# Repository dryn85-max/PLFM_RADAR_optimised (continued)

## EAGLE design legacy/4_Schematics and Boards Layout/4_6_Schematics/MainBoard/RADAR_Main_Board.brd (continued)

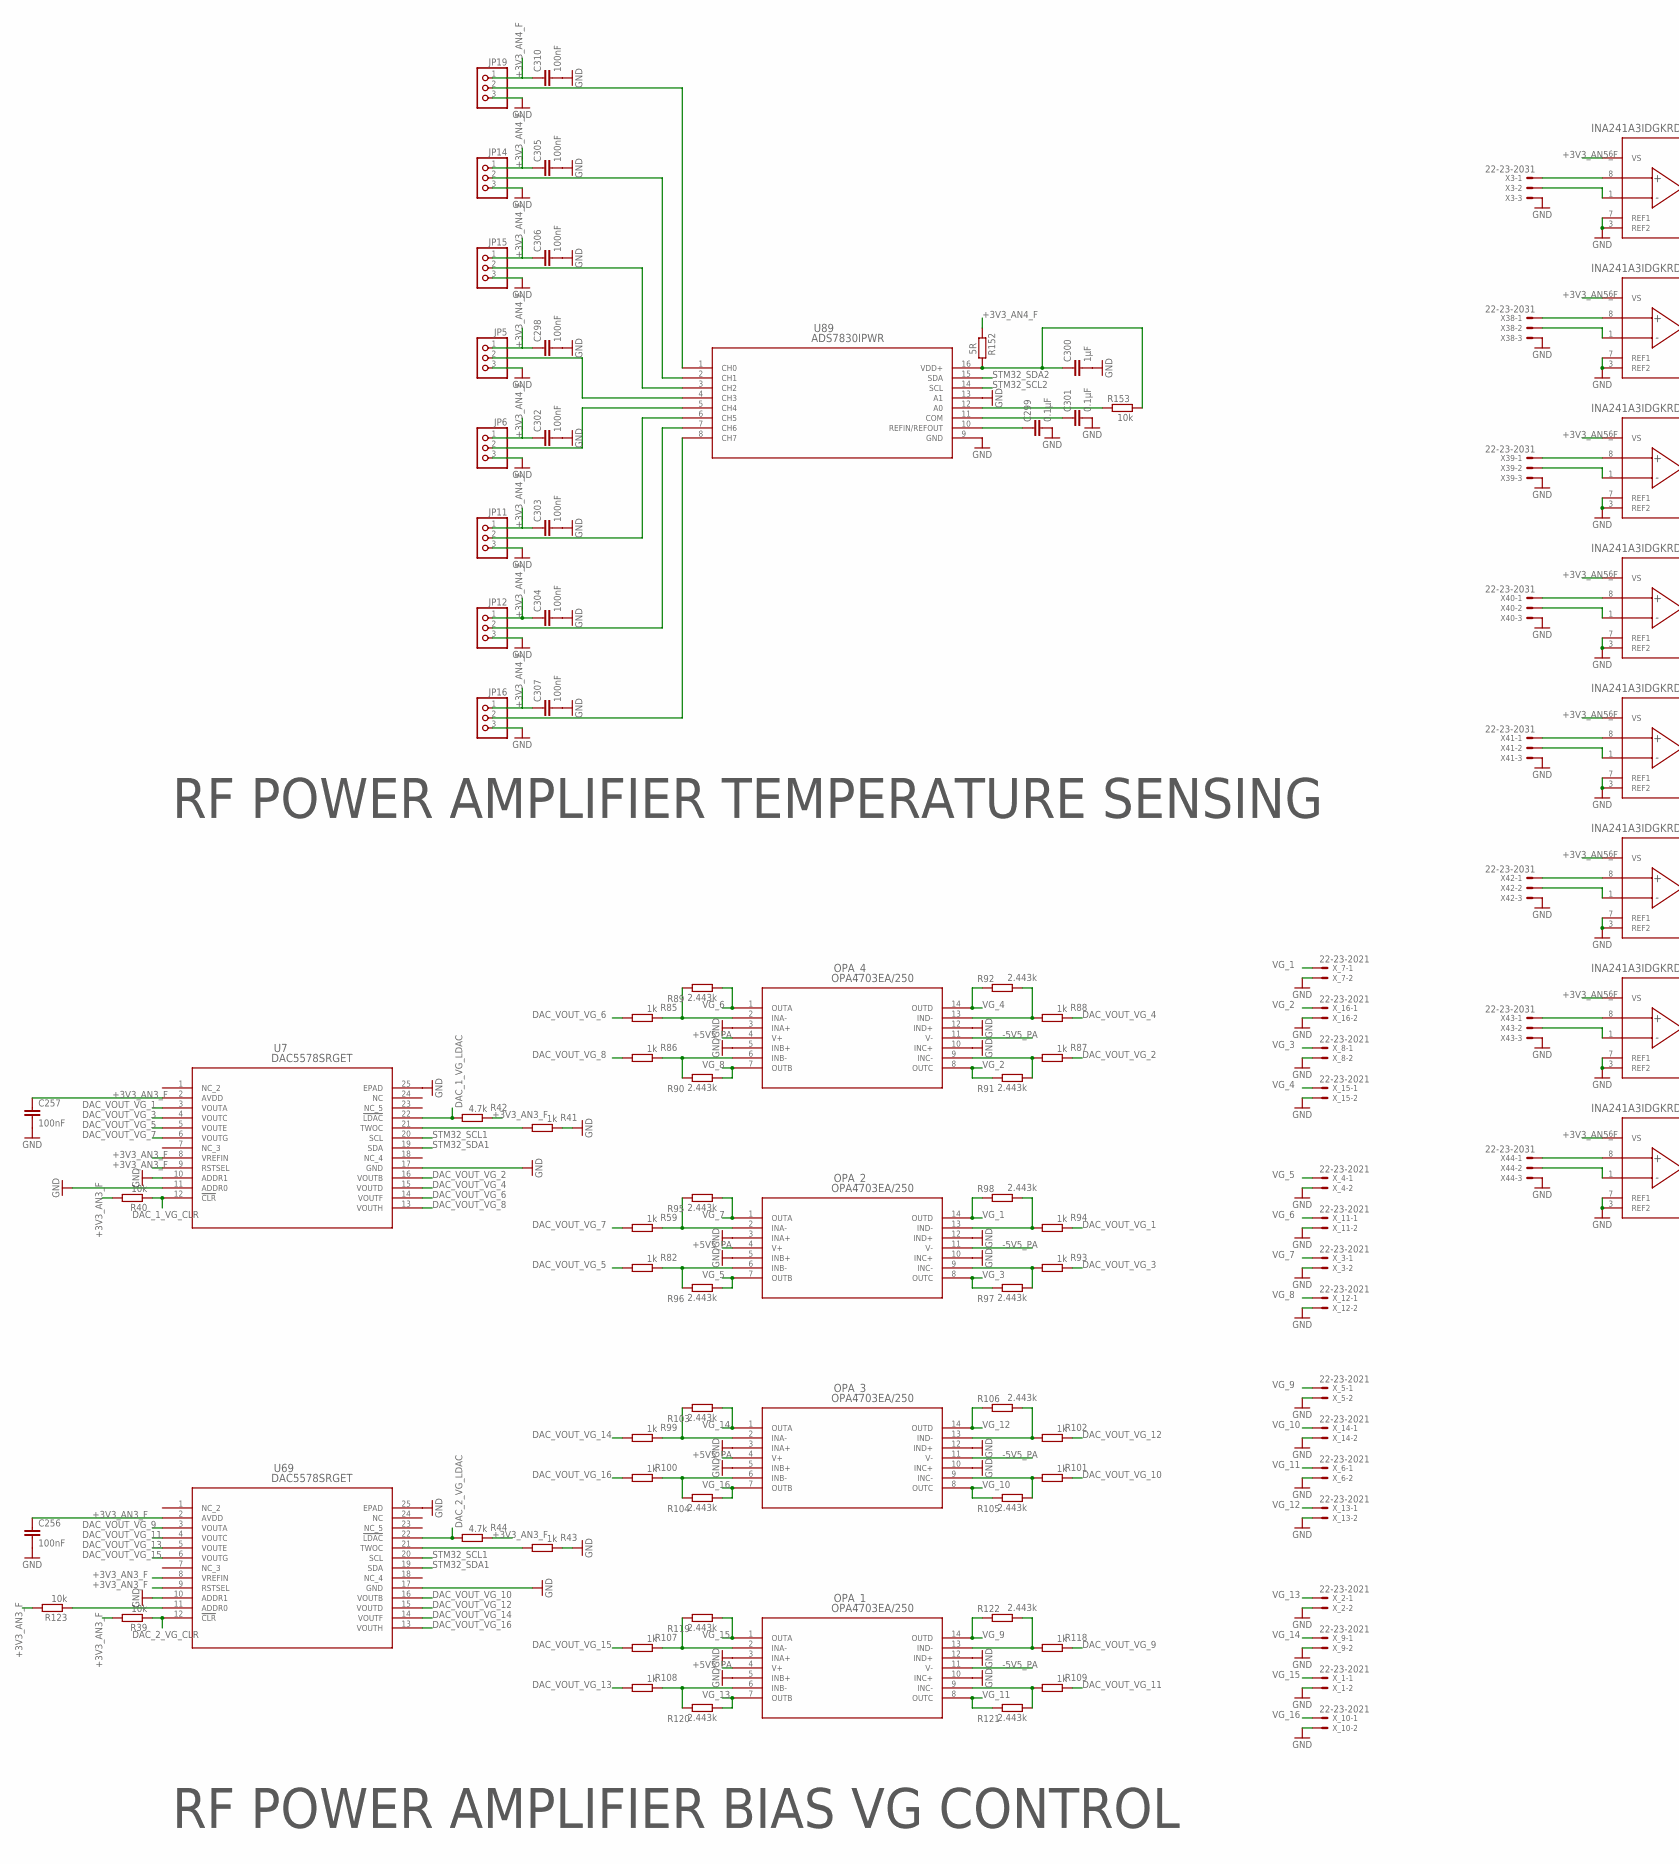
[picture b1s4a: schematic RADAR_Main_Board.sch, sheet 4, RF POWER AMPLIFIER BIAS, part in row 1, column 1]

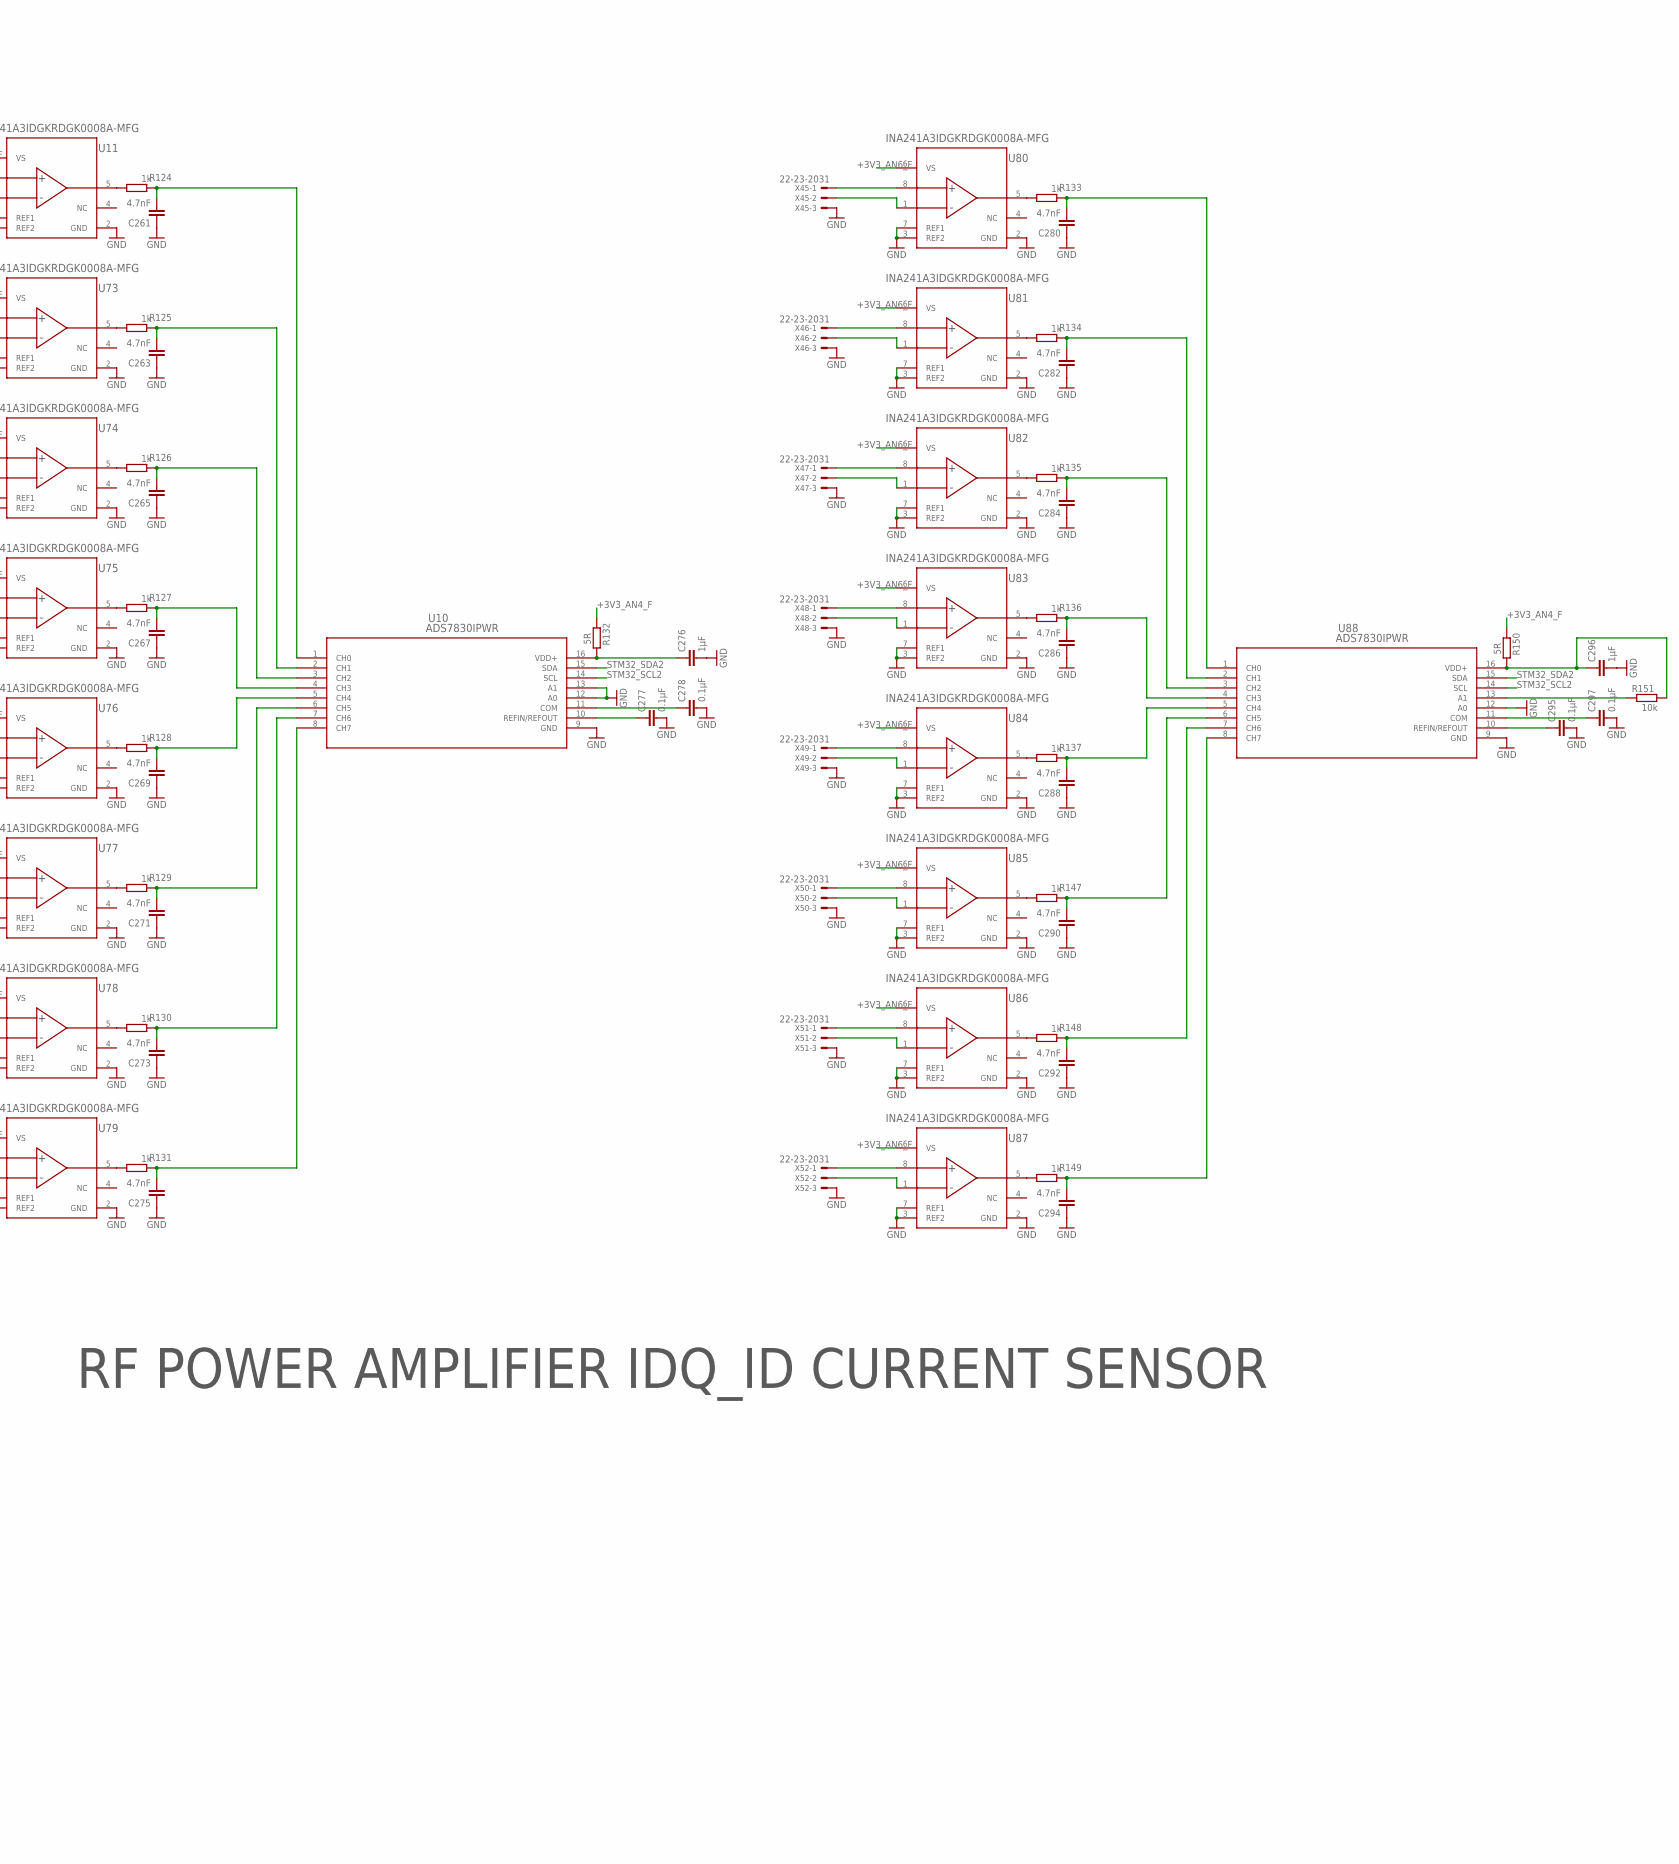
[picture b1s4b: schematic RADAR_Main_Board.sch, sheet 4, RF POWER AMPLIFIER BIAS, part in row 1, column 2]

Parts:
C256, C257, C298, C302, C303, C304, C305, C306, C307, C310: 100nF; C0201
C261, C263, C265, C267, C269, C271, C273, C275, C280, C282, C284, C286, C288, C290, C292, C294: 4.7nF; C0201
C276, C296, C300: 1µF; C0201
C277, C278, C295, C297, C299, C301: 0.1µF; C0201
JP5, JP6, JP11, JP12, JP14, JP15, JP16, JP19: PINHD-1X3; 1X03
OPA_1, OPA_2, OPA_3, OPA_4: OPA4703EA/250; PW14
R39, R40, R123, R151, R153: 10k; R0201
R41, R43, R59, R82, R85, R86, R87, R88, R93, R94, R99, R100, R101, R102, R107, R108, R109, R118, R124, R125, R126, R127, R128, R129, R130, R131, R133, R134, R135, R136, R137, R147, R148, R149: 1k; R0201
R42, R44: 4.7k; R0201
R89, R90, R91, R92, R95, R96, R97, R98, R103, R104, R105, R106, R119, R120, R121, R122: 2.443k; R0201
R132, R150, R152: 5R; R0201
U7, U69: DAC5578SRGET; RGE24_2P7X2P7
U10, U88, U89: ADS7830IPWR; PW16
U11, U73, U74, U75, U76, U77, U78, U79, U80, U81, U82, U83, U84, U85, U86, U87: INA241A3IDGKRDGK0008A-MFG; DGK0008A-MFG
X3, X38, X39, X40, X41, X42, X43, X44, X45, X46, X47, X48, X49, X50, X51, X52: 22-23-2031
X_1, X_2, X_3, X_4, X_5, X_6, X_7, X_8, X_9, X_10, X_11, X_12, X_13, X_14, X_15, X_16: 22-23-2021

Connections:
+3V3_AN3_F: C256.1, C257.1, R39.2, R40.2, R42.1, R44.1, R123.2, U7.2 (AVDD), U7.8 (VREFIN), U7.9 (RSTSEL), U69.2 (AVDD), U69.8 (VREFIN), U69.9 (RSTSEL); also elsewhere on the board
+3V3_AN4_F: C298.1, C302.1, C303.1, C304.1, C305.1, C306.1, C307.1, C310.1, JP5.1, JP6.1, JP11.1, JP12.1, JP14.1, JP15.1, JP16.1, JP19.1, R132.1, R150.1, R152.1; also elsewhere on the board
+3V3_AN5_F: U11.6 (VS), U73.6 (VS), U74.6 (VS), U75.6 (VS), U76.6 (VS), U77.6 (VS), U78.6 (VS), U79.6 (VS); also elsewhere on the board
+3V3_AN6_F: U80.6 (VS), U81.6 (VS), U82.6 (VS), U83.6 (VS), U84.6 (VS), U85.6 (VS), U86.6 (VS), U87.6 (VS); also elsewhere on the board
+5V5_PA: OPA_1.4 (V+), OPA_2.4 (V+), OPA_3.4 (V+), OPA_4.4 (V+); also elsewhere on the board
-5V5_PA: OPA_1.11 (V-), OPA_2.11 (V-), OPA_3.11 (V-), OPA_4.11 (V-); also elsewhere on the board
DAC_1_VG_CLR: R40.1, U7.12 (!CLR); also elsewhere on the board
DAC_1_VG_LDAC: R42.2, U7.22 (!LDAC); also elsewhere on the board
DAC_2_VG_CLR: R39.1, U69.12 (!CLR); also elsewhere on the board
DAC_2_VG_LDAC: R44.2, U69.22 (!LDAC); also elsewhere on the board
DAC_VOUT_VG_1: R94.1, U7.3 (VOUTA)
DAC_VOUT_VG_2: R87.1, U7.16 (VOUTB)
DAC_VOUT_VG_3: R93.1, U7.4 (VOUTC)
DAC_VOUT_VG_4: R88.1, U7.15 (VOUTD)
DAC_VOUT_VG_5: R82.2, U7.5 (VOUTE)
DAC_VOUT_VG_6: R85.2, U7.14 (VOUTF)
DAC_VOUT_VG_7: R59.2, U7.6 (VOUTG)
DAC_VOUT_VG_8: R86.2, U7.13 (VOUTH)
DAC_VOUT_VG_9: R118.1, U69.3 (VOUTA)
DAC_VOUT_VG_10: R101.1, U69.16 (VOUTB)
DAC_VOUT_VG_11: R109.1, U69.4 (VOUTC)
DAC_VOUT_VG_12: R102.1, U69.15 (VOUTD)
DAC_VOUT_VG_13: R108.2, U69.5 (VOUTE)
DAC_VOUT_VG_14: R99.2, U69.14 (VOUTF)
DAC_VOUT_VG_15: R107.2, U69.6 (VOUTG)
DAC_VOUT_VG_16: R100.2, U69.13 (VOUTH)
GND: C256.2, C257.2, C261.1, C263.1, C265.1, C267.1, C269.1, C271.1, C273.1, C275.1, C276.2, C277.2, C278.2, C280.1, C282.1, C284.1, C286.1, C288.1, C290.1, C292.1, C294.1, C295.2, C296.2, C297.2, C298.2, C299.2, C300.2, C301.2, C302.2, C303.2, C304.2, C305.2, C306.2, C307.2, C310.2, JP5.3, JP6.3, JP11.3, JP12.3, JP14.3, JP15.3, JP16.3, JP19.3, OPA_1.3 (INA+), OPA_1.5 (INB+), OPA_1.10 (INC+), OPA_1.12 (IND+), OPA_2.3 (INA+), OPA_2.5 (INB+), OPA_2.10 (INC+), OPA_2.12 (IND+), OPA_3.3 (INA+), OPA_3.5 (INB+), OPA_3.10 (INC+), OPA_3.12 (IND+), OPA_4.3 (INA+), OPA_4.5 (INB+), OPA_4.10 (INC+), OPA_4.12 (IND+), R41.1, R43.1, U7.10 (ADDR1), U7.11 (ADDR0), U7.17 (GND), U7.25 (EPAD), U10.9 (GND), U10.12 (A0), U10.13 (A1), U11.2 (GND), U11.3 (REF2), U11.7 (REF1), U69.10 (ADDR1), U69.17 (GND), U69.25 (EPAD), U73.2 (GND), U73.3 (REF2), U73.7 (REF1), U74.2 (GND), U74.3 (REF2), U74.7 (REF1), U75.2 (GND), U75.3 (REF2), U75.7 (REF1), U76.2 (GND), U76.3 (REF2), U76.7 (REF1), U77.2 (GND), U77.3 (REF2), U77.7 (REF1), U78.2 (GND), U78.3 (REF2), U78.7 (REF1), U79.2 (GND), U79.3 (REF2), U79.7 (REF1), U80.2 (GND), U80.3 (REF2), U80.7 (REF1), U81.2 (GND), U81.3 (REF2), U81.7 (REF1), U82.2 (GND), U82.3 (REF2), U82.7 (REF1), U83.2 (GND), U83.3 (REF2), U83.7 (REF1), U84.2 (GND), U84.3 (REF2), U84.7 (REF1), U85.2 (GND), U85.3 (REF2), U85.7 (REF1), U86.2 (GND), U86.3 (REF2), U86.7 (REF1), U87.2 (GND), U87.3 (REF2), U87.7 (REF1), U88.9 (GND), U88.12 (A0), U89.9 (GND), U89.13 (A1), X3.3, X38.3, X39.3, X40.3, X41.3, X42.3, X43.3, X44.3, X45.3, X46.3, X47.3, X48.3, X49.3, X50.3, X51.3, X52.3, X_1.2, X_2.2, X_3.2, X_4.2, X_5.2, X_6.2, X_7.2, X_8.2, X_9.2, X_10.2, X_11.2, X_12.2, X_13.2, X_14.2, X_15.2, X_16.2; also elsewhere on the board
unnamed: R123.1, U69.11 (ADDR0)
unnamed: R43.2, U69.21 (TWOC)
unnamed: OPA_4.2 (INA-), R85.1, R89.1
unnamed: U11.8 (IN+), X3.1
unnamed: OPA_4.6 (INB-), R86.1, R90.1
unnamed: U11.1 (IN-), X3.2
unnamed: R124.2, U11.5 (OUT)
unnamed: C261.2, R124.1, U10.1 (CH0)
unnamed: U73.8 (IN+), X38.1
unnamed: OPA_4.9 (INC-), R87.2, R91.2
unnamed: U73.1 (IN-), X38.2
unnamed: R125.2, U73.5 (OUT)
unnamed: OPA_4.13 (IND-), R88.2, R92.2
unnamed: C263.2, R125.1, U10.2 (CH1)
unnamed: U74.8 (IN+), X39.1
unnamed: U74.1 (IN-), X39.2
unnamed: R126.2, U74.5 (OUT)
unnamed: R41.2, U7.21 (TWOC)
unnamed: OPA_2.2 (INA-), R59.1, R95.1
unnamed: C265.2, R126.1, U10.3 (CH2)
unnamed: OPA_2.6 (INB-), R82.1, R96.1
unnamed: U75.8 (IN+), X40.1
unnamed: U75.1 (IN-), X40.2
unnamed: R127.2, U75.5 (OUT)
unnamed: OPA_2.9 (INC-), R93.2, R97.2
unnamed: C267.2, R127.1, U10.4 (CH3)
unnamed: U76.8 (IN+), X41.1
unnamed: OPA_2.13 (IND-), R94.2, R98.2
unnamed: U76.1 (IN-), X41.2
unnamed: R128.2, U76.5 (OUT)
unnamed: C269.2, R128.1, U10.5 (CH4)
unnamed: U77.8 (IN+), X42.1
unnamed: U77.1 (IN-), X42.2
unnamed: R129.2, U77.5 (OUT)
unnamed: OPA_3.2 (INA-), R99.1, R103.1
unnamed: C271.2, R129.1, U10.6 (CH5)
unnamed: OPA_3.6 (INB-), R100.1, R104.1
unnamed: U78.8 (IN+), X43.1
unnamed: U78.1 (IN-), X43.2
unnamed: R130.2, U78.5 (OUT)
unnamed: OPA_3.9 (INC-), R101.2, R105.2
unnamed: C273.2, R130.1, U10.7 (CH6)
unnamed: U79.8 (IN+), X44.1
unnamed: OPA_3.13 (IND-), R102.2, R106.2
unnamed: U79.1 (IN-), X44.2
unnamed: R131.2, U79.5 (OUT)
unnamed: C275.2, R131.1, U10.8 (CH7)
unnamed: C277.1, U10.10 (REFIN/REFOUT)
unnamed: C276.1, R132.2, U10.16 (VDD+)
unnamed: C278.1, U10.11 (COM)
unnamed: OPA_1.2 (INA-), R107.1, R119.1
unnamed: U80.8 (IN+), X45.1
unnamed: OPA_1.6 (INB-), R108.1, R120.1
unnamed: U80.1 (IN-), X45.2
unnamed: R133.2, U80.5 (OUT)
unnamed: C280.2, R133.1, U88.1 (CH0)
unnamed: OPA_1.9 (INC-), R109.2, R121.2
unnamed: U81.8 (IN+), X46.1
unnamed: U81.1 (IN-), X46.2
unnamed: OPA_1.13 (IND-), R118.2, R122.2
unnamed: R134.2, U81.5 (OUT)
unnamed: C282.2, R134.1, U88.2 (CH1)
unnamed: U82.8 (IN+), X47.1
unnamed: U82.1 (IN-), X47.2
unnamed: R135.2, U82.5 (OUT)
unnamed: C284.2, R135.1, U88.3 (CH2)
unnamed: U83.8 (IN+), X48.1
unnamed: U83.1 (IN-), X48.2
unnamed: R136.2, U83.5 (OUT)
unnamed: C286.2, R136.1, U88.4 (CH3)
unnamed: U84.8 (IN+), X49.1
unnamed: U84.1 (IN-), X49.2
unnamed: R137.2, U84.5 (OUT)
unnamed: C288.2, R137.1, U88.5 (CH4)
unnamed: U85.8 (IN+), X50.1
unnamed: U85.1 (IN-), X50.2
unnamed: R147.2, U85.5 (OUT)
unnamed: C290.2, R147.1, U88.6 (CH5)
unnamed: U86.8 (IN+), X51.1
unnamed: U86.1 (IN-), X51.2
unnamed: R148.2, U86.5 (OUT)
unnamed: C292.2, R148.1, U88.7 (CH6)
unnamed: U87.8 (IN+), X52.1
unnamed: U87.1 (IN-), X52.2
unnamed: R149.2, U87.5 (OUT)
unnamed: C294.2, R149.1, U88.8 (CH7)
unnamed: C295.1, U88.10 (REFIN/REFOUT)
unnamed: C296.1, R150.2, R151.2, U88.16 (VDD+)
unnamed: C297.1, U88.11 (COM)
unnamed: R151.1, U88.13 (A1)
unnamed: R153.1, U89.12 (A0)
unnamed: JP5.2, U89.4 (CH3)
unnamed: JP6.2, U89.5 (CH4)
unnamed: JP19.2, U89.1 (CH0)
unnamed: JP12.2, U89.7 (CH6)
unnamed: JP14.2, U89.2 (CH1)
unnamed: JP16.2, U89.8 (CH7)
unnamed: C299.1, U89.10 (REFIN/REFOUT)
unnamed: C300.1, R152.2, R153.2, U89.16 (VDD+)
unnamed: C301.1, U89.11 (COM)
unnamed: JP11.2, U89.6 (CH5)
unnamed: JP15.2, U89.3 (CH2)
STM32_SCL1: U7.20 (SCL), U69.20 (SCL); also elsewhere on the board
STM32_SCL2: U10.14 (SCL), U88.14 (SCL), U89.14 (SCL); also elsewhere on the board
STM32_SDA1: U7.19 (SDA), U69.19 (SDA); also elsewhere on the board
STM32_SDA2: U10.15 (SDA), U88.15 (SDA), U89.15 (SDA); also elsewhere on the board
VG_1: OPA_2.14 (OUTD), R98.1, X_7.1
VG_2: OPA_4.8 (OUTC), R91.1, X_16.1
VG_3: OPA_2.8 (OUTC), R97.1, X_8.1
VG_4: OPA_4.14 (OUTD), R92.1, X_15.1
VG_5: OPA_2.7 (OUTB), R96.2, X_4.1
VG_6: OPA_4.1 (OUTA), R89.2, X_11.1
VG_7: OPA_2.1 (OUTA), R95.2, X_3.1
VG_8: OPA_4.7 (OUTB), R90.2, X_12.1
VG_9: OPA_1.14 (OUTD), R122.1, X_5.1
VG_10: OPA_3.8 (OUTC), R105.1, X_14.1
VG_11: OPA_1.8 (OUTC), R121.1, X_6.1
VG_12: OPA_3.14 (OUTD), R106.1, X_13.1
VG_13: OPA_1.7 (OUTB), R120.2, X_2.1
VG_14: OPA_3.1 (OUTA), R103.2, X_9.1
VG_15: OPA_1.1 (OUTA), R119.2, X_1.1
VG_16: OPA_3.7 (OUTB), R104.2, X_10.1

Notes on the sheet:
RF POWER AMPLIFIER IDQ_ID CURRENT SENSOR
RF POWER AMPLIFIER BIAS VG CONTROL
RF POWER AMPLIFIER TEMPERATURE SENSING

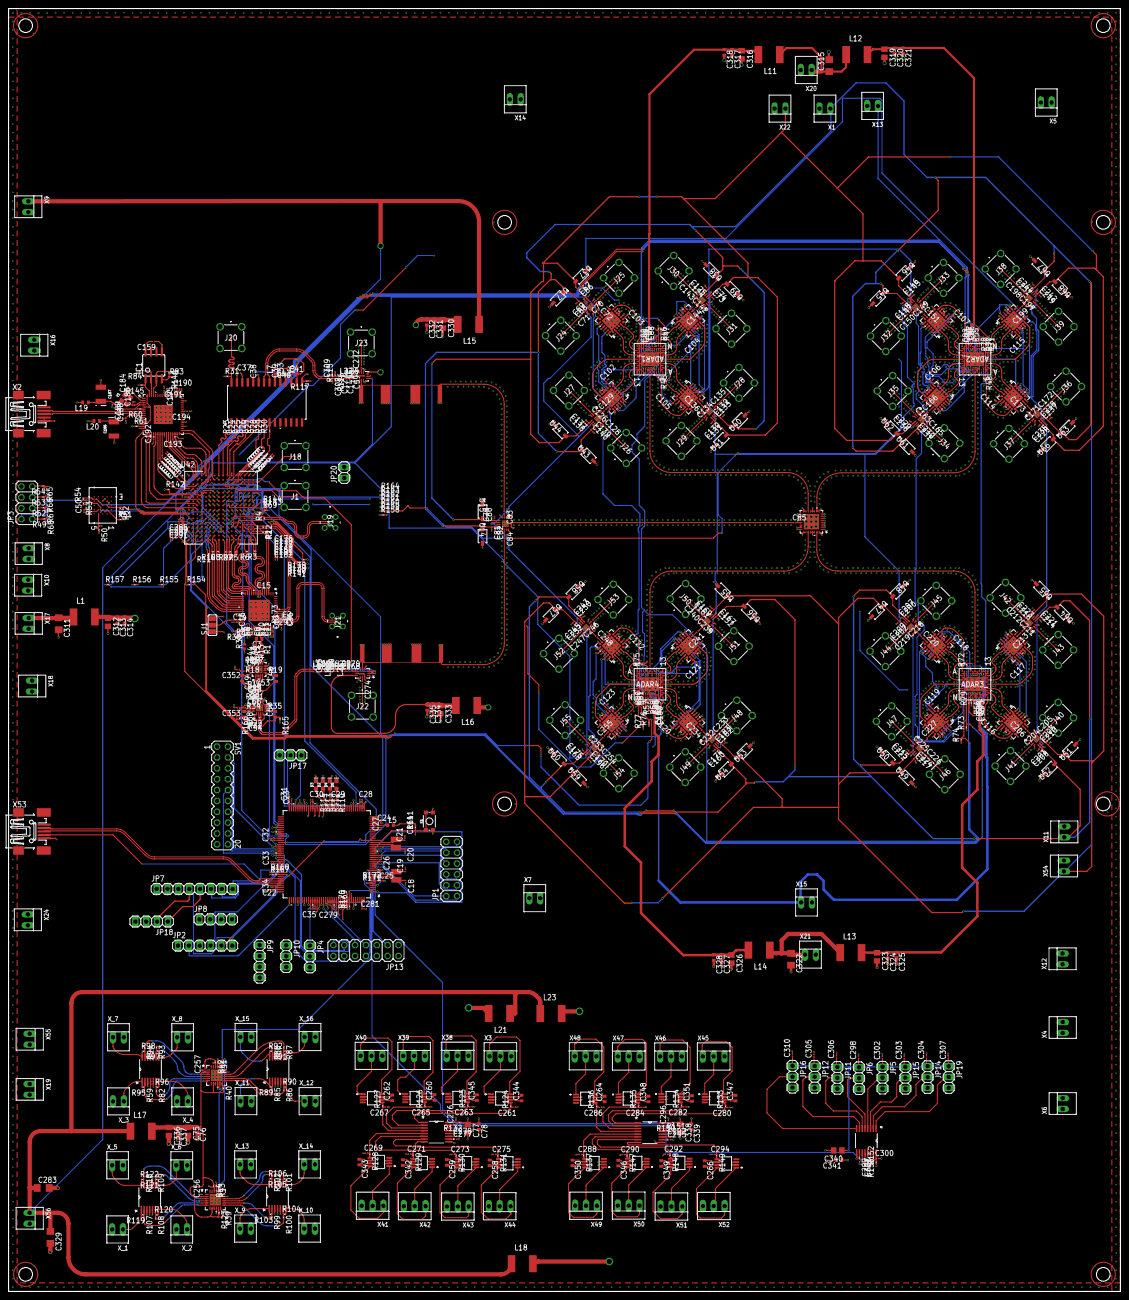
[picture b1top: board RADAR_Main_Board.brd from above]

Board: 10 copper layers, 260.0 x 300.0 mm, 791 parts (0 on the bottom side), 649 nets.

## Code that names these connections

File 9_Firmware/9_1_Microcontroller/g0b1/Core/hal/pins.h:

/* Pin map: NUCLEO-G0B1RE (STM32G0B1RET6). Included only by the target HAL sources and main.c.
 * Role -> MCU pin. AF numbers exist in the vendored HAL (GPIO_AF0_SPI1/SPI2,
 * GPIO_AF6_I2C1, GPIO_AF1_USART2); the pin<->AF assignment itself comes from the
 * G0B1 datasheet alternate-function table (verify before finalising the README).
 *
 *  ADAR1000 SPI2 SCK/MISO/MOSI    PB13 / PB14 / PB15 (AF0), 16 MHz (64/4)
 *  ADAR CS0..CS3                  PB12, PB11, PB10, PB2
 *  PLL SPI1 SCK/MISO/MOSI         PB3 / PB4 / PB5 (AF0), 8 MHz (64/8)
 *  PLL CS / CE / LD               PB1 / PB0 (out) / PB6 (in)
 *  I2C1 SCL / SDA (ADS7830)       PB8 / PB9 (AF6), 100 kHz
 *  USART2 TX / RX (ST-LINK VCP)   PA2 / PA3 (AF1), 115200 8N1
 *  LED LD4                        PA5
 *  EN_FPGA, EN_LO, EN_ADAR        PA0, PA1, PA4 (active high)
 *  EN_ADTR_VDD_SW, EN_ADTR_VSS_SW PA6, PA7
 *  EN_LNA (3V3), EN_PA (5 V)      PA8, PC8
 *  FPGA DIG0..DIG4 (outputs)      PC0..PC4: new_chirp, new_elevation,
 *                                 new_azimuth, mixers_enable, fpga_reset_n
 *  FPGA DIG5..DIG7 (inputs)       PC5..PC7: agc_saturation, agc_enable, reserved
 *
 * Not used (Nucleo-reserved): PC13 (B1), PC14/PC15 (LSE), PF0/PF1 (HSE pads),
 * PA13/PA14 (SWD), PA11/PA12 (future USB), PA9/PA10 (remappable onto the PA11/PA12
 * pads on STM32G0). tests/test_pins.c enforces this.
 *
 * Mapping table (port, pin, direction, idle level) is pure data in pins_table.c;
 * hal_gpio.c applies it on the target.
 * Chip selects idle HIGH (active low); every other output idles LOW.
 */
#ifndef PINS_H
#define PINS_H

#define PIN_FPGA_PORT_SHIFT 0   /* DIG0 is PC0: IDR bits 0..7 = DIG0..7 */

#endif
